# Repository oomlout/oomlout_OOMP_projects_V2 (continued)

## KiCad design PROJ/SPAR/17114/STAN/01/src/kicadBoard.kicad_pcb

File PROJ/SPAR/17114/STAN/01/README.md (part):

Contents
========

* [PRPR17114 > Qwiic Cellular Notecarrier](#prpr17114--qwiic-cellular-notecarrier)
	* [OOMP Parts](#oomp-parts)
	* [Images](#images)
	* [Tags](#tags)
  
![][im]
# PRPR17114 > Qwiic Cellular Notecarrier

- ID: PROJ-SPAR-17114-STAN-01
- Hex ID: PRPR17114
- Name: Qwiic Cellular Notecarrier
- Path: oomlout_OOMP_projects_V2/PROJ/SPAR/17114/STAN/01/
- Description: Qwiic Cellular Notecarrier
- Long Link: [http://oom.lt/PROJ-SPAR-17114-STAN-01](http://oom.lt/PROJ-SPAR-17114-STAN-01)
- Short Link: [http://oom.lt/PRPR17114](http://oom.lt/PRPR17114)

## OOMP Parts

|Image|OOMP ID|Designators|
| :--- | :--- | :--- |
||[CAPC-0603-X-NF100-V50](https://github.com/oomlout/oomlout_OOMP_parts_V2/tree/main/CAPC/0603/X/NF100/V50/)|[C6](https://github.com/oomlout/oomlout_OOMP_parts_V2/tree/main/CAPC/0603/X/NF100/V50/)|
||CAPC-0603-X-NF220-V25|C7|
||[CAPC-0603-X-UF1-V50](https://github.com/oomlout/oomlout_OOMP_parts_V2/tree/main/CAPC/0603/X/UF1/V50/)|[C5,C17,C18](https://github.com/oomlout/oomlout_OOMP_parts_V2/tree/main/CAPC/0603/X/UF1/V50/)|
||[CAPC-0603-X-UF47D-V16](https://github.com/oomlout/oomlout_OOMP_parts_V2/tree/main/CAPC/0603/X/UF47D/V16/)|[C4,C3](https://github.com/oomlout/oomlout_OOMP_parts_V2/tree/main/CAPC/0603/X/UF47D/V16/)|
||CAPX-1210-X-UF22-01|C1|
||DIOD-S323-X-UNMATCHED-01|D4,D1,D6|
||[HEAD-I01-X-PI01-01](https://github.com/oomlout/oomlout_OOMP_parts_V2/tree/main/HEAD/I01/X/PI01/01/)|[J13,J9](https://github.com/oomlout/oomlout_OOMP_parts_V2/tree/main/HEAD/I01/X/PI01/01/)|
||[HEAD-I01-X-PI02-01](https://github.com/oomlout/oomlout_OOMP_parts_V2/tree/main/HEAD/I01/X/PI02/01/)|[J4,J2,J7](https://github.com/oomlout/oomlout_OOMP_parts_V2/tree/main/HEAD/I01/X/PI02/01/)|
||[HEAD-I01-X-PI04-01](https://github.com/oomlout/oomlout_OOMP_parts_V2/tree/main/HEAD/I01/X/PI04/01/)|[J14](https://github.com/oomlout/oomlout_OOMP_parts_V2/tree/main/HEAD/I01/X/PI04/01/)|
||[HEAD-I01-X-PI06-01](https://github.com/oomlout/oomlout_OOMP_parts_V2/tree/main/HEAD/I01/X/PI06/01/)|[J6](https://github.com/oomlout/oomlout_OOMP_parts_V2/tree/main/HEAD/I01/X/PI06/01/)|
||[HEAD-I01-X-PI07-01](https://github.com/oomlout/oomlout_OOMP_parts_V2/tree/main/HEAD/I01/X/PI07/01/)|[J16](https://github.com/oomlout/oomlout_OOMP_parts_V2/tree/main/HEAD/I01/X/PI07/01/)|
||[HEAD-I01-X-PI10-01](https://github.com/oomlout/oomlout_OOMP_parts_V2/tree/main/HEAD/I01/X/PI10/01/)|[J5](https://github.com/oomlout/oomlout_OOMP_parts_V2/tree/main/HEAD/I01/X/PI10/01/)|
||HEAD-I01-X-UNMATCHED-01|J10,J12,J15|
||[HEAD-JSTSH-X-PI04-RS](https://github.com/oomlout/oomlout_OOMP_parts_V2/tree/main/HEAD/JSTSH/X/PI04/RS/)|[J8,J3](https://github.com/oomlout/oomlout_OOMP_parts_V2/tree/main/HEAD/JSTSH/X/PI04/RS/)|
||[LEDS-0603-R-STAN-01](https://github.com/oomlout/oomlout_OOMP_parts_V2/tree/main/LEDS/0603/R/STAN/01/)|[D5](https://github.com/oomlout/oomlout_OOMP_parts_V2/tree/main/LEDS/0603/R/STAN/01/)|
||[LEDS-0603-Y-STAN-01](https://github.com/oomlout/oomlout_OOMP_parts_V2/tree/main/LEDS/0603/Y/STAN/01/)|[D2](https://github.com/oomlout/oomlout_OOMP_parts_V2/tree/main/LEDS/0603/Y/STAN/01/)|
||[RESE-0603-X-O102-01](https://github.com/oomlout/oomlout_OOMP_parts_V2/tree/main/RESE/0603/X/O102/01/)|[R7,R11](https://github.com/oomlout/oomlout_OOMP_parts_V2/tree/main/RESE/0603/X/O102/01/)|
||[RESE-0603-X-O222-01](https://github.com/oomlout/oomlout_OOMP_parts_V2/tree/main/RESE/0603/X/O222/01/)|[R6,R4,R1](https://github.com/oomlout/oomlout_OOMP_parts_V2/tree/main/RESE/0603/X/O222/01/)|
||RESE-0603-X-O472-01|R3,R2|
||UNMATCHED-SO235-X-UNMATCHED-01|U1,U2|
||UNMATCHED-UNMATCHED-X-UNMATCHED-01|S1,E3,E4,U4|
||USBS-UNMATCHED-X-UNMATCHED-01|J1|
||||

## Images

|kicadPcb3dFront<br>|kicadPcb3dBack<br>|kicadPcb3d<br>|pcbdraw<br>|
| :---: | :---: | :---: | :---: |
|pcbdrawBack<br>||||

## Tags

|Tag Name|Tag Code|Tag Value|
| :--- | :--- | :--- |
|OOMP Type|oompType|PROJ|
|OOMP Size|oompSize|SPAR|
|OOMP Color|oompColor|17114|
|OOMP Description|oompDesc|STAN|
|OOMP Index|oompIndex|01|
|Full OOMP ID|oompID|PROJ-SPAR-17114-STAN-01|
|Hex ID (short code)|hexID|PRPR17114|
|name|name|Qwiic Cellular Notecarrier|
|gitRepo|gitRepo|https://github.com/sparkfun/Qwiic_Cellular-Notecarrier|
|gitName|gitName|Qwiic_Cellular-Notecarrier|
|eagleBoard|eagleBoard|/Hardware/Qwiic-Cellular-Notepad.brd|
|eagleSchem|eagleSchem|/Hardware/Qwiic-Cellular-Notepad.sch|
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
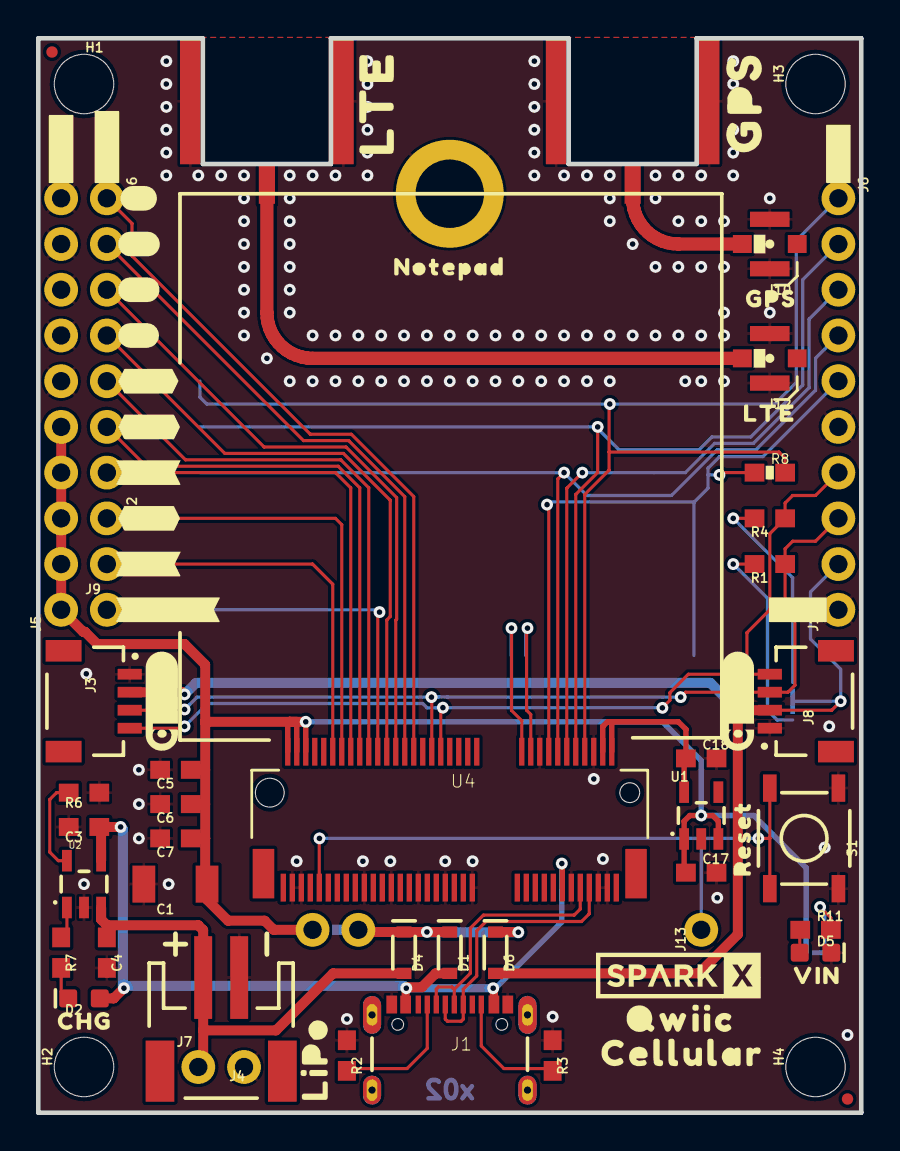
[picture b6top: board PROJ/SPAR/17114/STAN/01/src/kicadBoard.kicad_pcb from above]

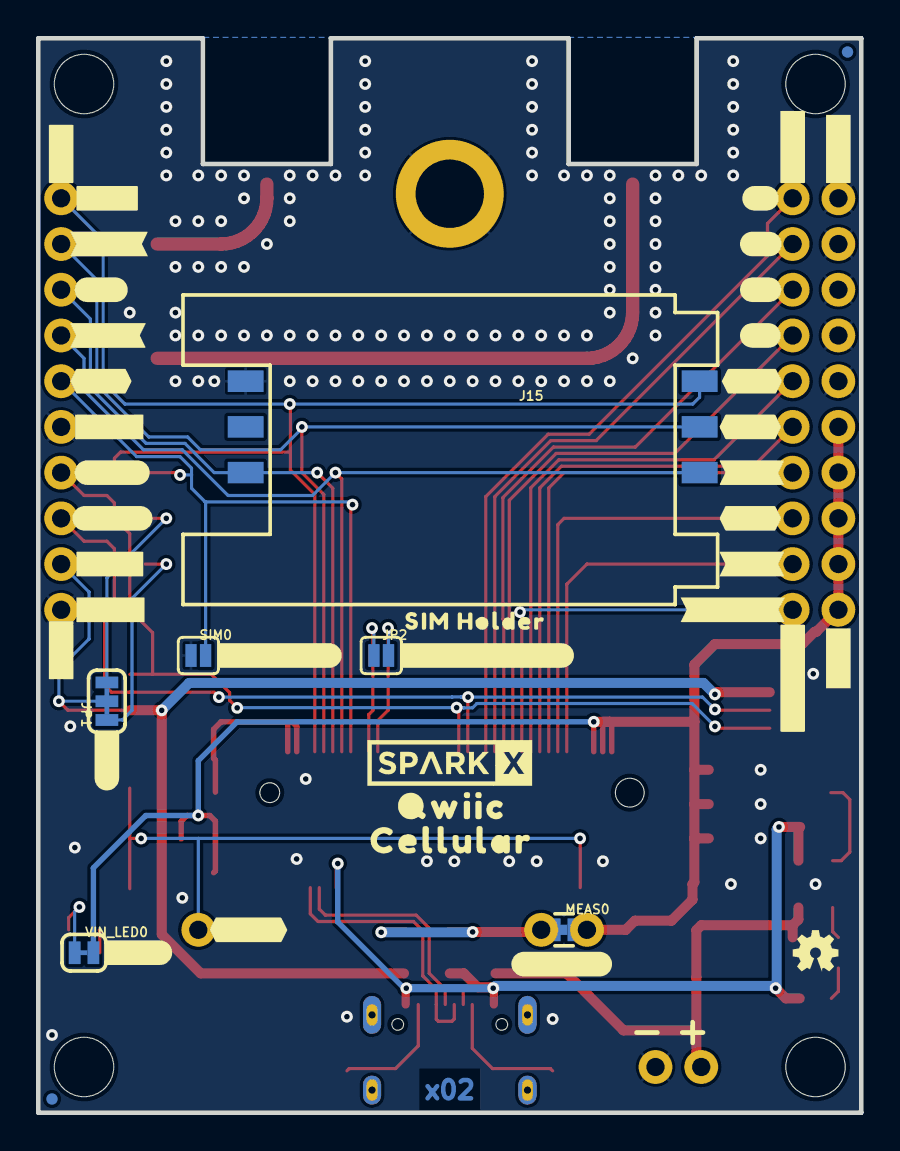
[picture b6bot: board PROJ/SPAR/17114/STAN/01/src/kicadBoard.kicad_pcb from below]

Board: 2 copper layers, 45.7 x 59.7 mm, 122 parts (45 on the bottom side), 40 nets.

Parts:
C1: 22uF; 1210
C3, C4: 4.7uF; 0603
C5, C17, C18: 1.0uF; 0603
C6: 0.1uF; 0603
C7: 0.22uF; 0603
D1, D4, D6: 3A/10V/280mV; SOD-323
D2: Yellow; LED-0603
D5: RED; LED-0603
E3, E4: SMA; SMA-EDGE-SMD
FD1, FD2, FD3, FD4: FIDUCIALUFIDUCIAL; FIDUCIAL-MICRO
FRAME1: FRAME-LEDGER; CREATIVE_COMMONS
H1, H2, H3, H4: STAND-OFF
H5: STAND-OFF; STAND-OFF-REFLOW-M2.5
J1: USB-C-16P-2LAYER-PADS
J2, J7: 1X02_NO_SILK
J3, J8: QWIIC_RIGHT_ANGLE; JST04_1MM_RA
J4: JST-2-SMD
J5: 1X10_NO_SILK
J6: External SIM; 1X06_NO_SILK
J9, J13: 1X01_NO_SILK
J10, J12: U.FL
J14: I2C; 1X04_NO_SILK
J15: SIM Socket; SIMHOLDER
J16: 1X07_NO_SILK
JP1: SMT-JUMPER_3_2-NC_TRACE_SILK
JP2: GPS_ANT_PWR; SMT-JUMPER_2_NO_SILK
LOGO2, LOGO5: QWIIC_LOGO_CONNECTOR; QWIIC_5.5MM
LOGO3: OSHW-LOGOMINI; OSHW-LOGO-MINI
MEAS0: COMBO-JUMPER_2_NC_TRACE
R1, R4, R6: 2.2k; 0603
R2, R3: 5.1k; 0603
R7, R11: 1k; 0603
R8: DNP; 0603-RES
S1: Reset; TACTILE_SWITCH_SMD_5.2MM
SIM0: SMT-JUMPER_2_NO_SILK
U1: STLQ015-3.3V; SOT23-5
U2: MCP73831; SOT23-5
U4: BLUES NOTECARD; M.2-CONNECTOR-E
U$1, U$41: #1#1
U$2: #3V3#2
U$3, U$18, U$22: #GND#0
U$4, U$42: #2#2
U$5, U$43: #3#3
U$6, U$44: #4#4
U$7: GPS_0
U$8: #SERIAL#1
U$9, U$53: #I�C_#0
U$10: #I�C#0
U$11, U$40: #AUX#0
U$12: LTE_1
U$13: #GND#3
U$14, U$46: #RX#6
U$15: LIPO0
U$16, U$47: #TX#5
U$17: #SCL#1
U$19, U$45: #EN#0
U$20: NOTEPAD0
U$21: #SDA#0
U$23: #VIN#0
U$24: #VACT_GPS#0
U$25: #SIM_CD#0
U$26, U$31: QWIIC0
U$27: SIM_HOLDER0
U$28: #MEAS#3
U$29, U$32: CELLULAR1
U$30: #RST#0
U$33: #VIN#1
U$34: ##CD##1
U$35: #1V8#4
U$36: #CLK#3
U$37: #IO#2
U$38: #RST#5
U$39, U$51: #SIM#0
U$48, U$52: #RX#0
U$49, U$54: #TX#1
U$50, U$55: #ATTN#2
U$56, U$57: SPARKX-LOGO4; SPARKX-MEDIUM
U$58: GPS0
U$59: LTE1
U$92: RESET1
U$94: VIN1
U$96: CHG1
VIN_LED0: SMT-JUMPER_2_NC_TRACE_SILK

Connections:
3.3V: D6.A, J3.2, J8.2, J14.2, JP1.2
ATTN: J9.1, U4.54
AUX1: J16.1, U4.46
AUX2: J16.2, U4.48
AUX3: J16.3, U4.50
AUX4: J16.4, U4.52
AUX_EN: J16.5, U4.56
AUX_RX: J16.6, U4.58
AUX_TX: J16.7, U4.60
CHG_LED: R7.1, U2.1
GND: C1.2, C3.2, C4.2, C5.2, C6.2, C7.2, C17.2, C18.2, D5.C, E3.GND@0, E3.GND@1, E4.GND@0, E4.GND@1, H5.1, J1.GND, J1.GND2, J3.1, J4.1, J5.6, J5.7, J5.8, J5.9, J5.10, J6.6, J7.2, J8.1, J10.1, J10.2, J12.1, J12.2, J14.1, J15.C5, R2.1, R3.1, R6.1, S1.1, S1.2, SIM0.1, U1.2, U2.2, U4.3, U4.5, U4.6, U4.11, U4.18, U4.33, U4.39, U4.45, U4.51, U4.57, U4.71, U4.73
unnamed: JP1.3, R4.2
unnamed: JP1.1, R1.2
unnamed: D2.C, R7.2
unnamed: D5.A, R11.1
unnamed: R11.2, VIN_LED0.1
unnamed: R6.2, U2.5
unnamed: J1.A5, R2.2
unnamed: J1.B5, R3.2
RF_GPS: E4.SIG, J10.FEED
RF_LTE: E3.SIG, J12.FEED
RX: J2.1, U4.62
SCL: J3.4, J8.4, J14.4, R4.1, U4.40
SDA: J3.3, J8.3, J14.3, R1.1, U4.42
SIM_CLK: J6.4, J15.C3, U4.14
SIM_IO: J6.3, J15.C7, U4.12
SIM_RST: J6.2, J15.C2, U4.10
SIM_VCC: J6.1, J15.C1, R8.2, U4.8
SIM_~CD: J6.5, R8.1, SIM0.2, U4.16
TX: J2.2, U4.64
USB_D+: J1.A6, J1.B6, U4.7
USB_D-: J1.A7, J1.B7, U4.9
VACT_GPS_IN: JP2.2, U4.22
VACT_GPS_OUT: JP2.1, U4.20
VIN: C1.1, C5.1, C6.1, C7.1, C17.1, J5.1, J5.2, J5.3, J5.4, J5.5, MEAS0.2, MEAS0.4, U1.1, U1.3, U4.70, U4.72, U4.74, VIN_LED0.2
VIN1: D1.C, D4.C, D6.C, MEAS0.1, MEAS0.3
VIO: C18.1, U1.5, U4.2, U4.4
V_BATT: C4.1, D4.A, J4.2, J7.1, U2.3
V_USB: C3.1, D1.A, D2.A, J1.VBUS1, J1.VBUS2, U2.4, U4.13
~RESET: J13.1, S1.3, S1.4, U4.67

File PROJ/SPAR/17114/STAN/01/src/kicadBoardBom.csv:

"Id";"Designator";"Package";"Quantity";"Designation";"Supplier and ref";
1;"U$31,U$26";"QWIIC0";2;"";;;
2;"FD2,FD1,FD3,FD4";"FIDUCIAL-MICRO";4;"FIDUCIALUFIDUCIAL";;;
3;"U$53,U$9";"#I�C_#0";2;"";;;
4;"H2,H4,H3,H1";"STAND-OFF";4;"STAND-OFF";;;
5;"U$96";"CHG1";1;"";;;
6;"J5";"1X10_NO_SILK";1;"";;;
7;"R3,R2";"0603";2;"5.1k";;;
8;"U$20";"NOTEPAD0";1;"";;;
9;"U$92";"RESET1";1;"";;;
10;"U$50,U$55";"#ATTN#2";2;"";;;
11;"R7,R11";"0603";2;"1k";;;
12;"J14";"1X04_NO_SILK";1;"I2C";;;
13;"U$22,U$18,U$3";"#GND#0";3;"";;;
14;"U$51,U$39";"#SIM#0";2;"";;;
15;"J1";"USB-C-16P-2LAYER-PADS";1;"";;;
16;"U$7";"GPS_0";1;"";;;
17;"U1";"SOT23-5";1;"STLQ015-3.3V";;;
18;"S1";"TACTILE_SWITCH_SMD_5.2MM";1;"Reset";;;
19;"R8";"0603-RES";1;"DNP";;;
20;"J13,J9";"1X01_NO_SILK";2;"";;;
21;"D4,D1,D6";"SOD-323";3;"3A/10V/280mV";;;
22;"J16";"1X07_NO_SILK";1;"";;;
23;"E3,E4";"SMA-EDGE-SMD";2;"SMA";;;
24;"U$59";"LTE1";1;"";;;
25;"R6,R4,R1";"0603";3;"2.2k";;;
26;"U$40,U$11";"#AUX#0";2;"";;;
27;"U$94";"VIN1";1;"";;;
28;"C1";"1210";1;"22uF";;;
29;"U$58";"GPS0";1;"";;;
30;"J4";"JST-2-SMD";1;"";;;
31;"U$41,U$1";"#1#1";2;"";;;
32;"LOGO5,LOGO2";"QWIIC_5.5MM";2;"QWIIC_LOGO_CONNECTOR";;;
33;"J6";"1X06_NO_SILK";1;"External SIM";;;
34;"U$56,U$57";"SPARKX-MEDIUM";2;"SPARKX-LOGO4";;;
35;"J2,J7";"1X02_NO_SILK";2;"";;;
36;"U$44,U$6";"#4#4";2;"";;;
37;"U$48,U$52";"#RX#0";2;"";;;
38;"U$49,U$54";"#TX#1";2;"";;;
39;"J8,J3";"JST04_1MM_RA";2;"QWIIC_RIGHT_ANGLE";;;
40;"C6";"0603";1;"0.1uF";;;
41;"U$46,U$14";"#RX#6";2;"";;;
42;"U$12";"LTE_1";1;"";;;
43;"U$42,U$4";"#2#2";2;"";;;
44;"J10,J12";"U.FL";2;"U.FL";;;
45;"U$43,U$5";"#3#3";2;"";;;
46;"H5";"STAND-OFF-REFLOW-M2.5";1;"STAND-OFF";;;
47;"U2";"SOT23-5";1;"MCP73831";;;
48;"U4";"M.2-CONNECTOR-E";1;"BLUES NOTECARD";;;
49;"C4,C3";"0603";2;"4.7uF";;;
50;"U$47,U$16";"#TX#5";2;"";;;
51;"C5,C17,C18";"0603";3;"1.0uF";;;
52;"U$45,U$19";"#EN#0";2;"";;;
53;"D5";"LED-0603";1;"RED";;;
54;"FRAME1";"CREATIVE_COMMONS";1;"FRAME-LEDGER";;;
55;"U$29,U$32";"CELLULAR1";2;"";;;
56;"D2";"LED-0603";1;"Yellow";;;
57;"C7";"0603";1;"0.22uF";;;
58;"U$15";"LIPO0";1;"";;;
59;"MEAS0";"COMBO-JUMPER_2_NC_TRACE";1;"";;;
60;"JP1";"SMT-JUMPER_3_2-NC_TRACE_SILK";1;"";;;
61;"U$25";"#SIM_CD#0";1;"";;;
62;"LOGO3";"OSHW-LOGO-MINI";1;"OSHW-LOGOMINI";;;
63;"SIM0";"SMT-JUMPER_2_NO_SILK";1;"";;;
64;"U$36";"#CLK#3";1;"";;;
65;"U$37";"#IO#2";1;"";;;
66;"JP2";"SMT-JUMPER_2_NO_SILK";1;"GPS_ANT_PWR";;;
67;"U$2";"#3V3#2";1;"";;;
68;"U$30";"#RST#0";1;"";;;
69;"U$23";"#VIN#0";1;"";;;
70;"J15";"SIMHOLDER";1;"SIM Socket";;;
71;"U$28";"#MEAS#3";1;"";;;
72;"U$17";"#SCL#1";1;"";;;
73;"U$8";"#SERIAL#1";1;"";;;
74;"U$21";"#SDA#0";1;"";;;
75;"U$35";"#1V8#4";1;"";;;
76;"U$33";"#VIN#1";1;"";;;
77;"U$38";"#RST#5";1;"";;;
78;"U$27";"SIM_HOLDER0";1;"";;;
79;"VIN_LED0";"SMT-JUMPER_2_NC_TRACE_SILK";1;"";;;
80;"U$10";"#I�C#0";1;"";;;
81;"U$13";"#GND#3";1;"";;;
82;"U$24";"#VACT_GPS#0";1;"";;;
83;"U$34";"##CD##1";1;"";;;

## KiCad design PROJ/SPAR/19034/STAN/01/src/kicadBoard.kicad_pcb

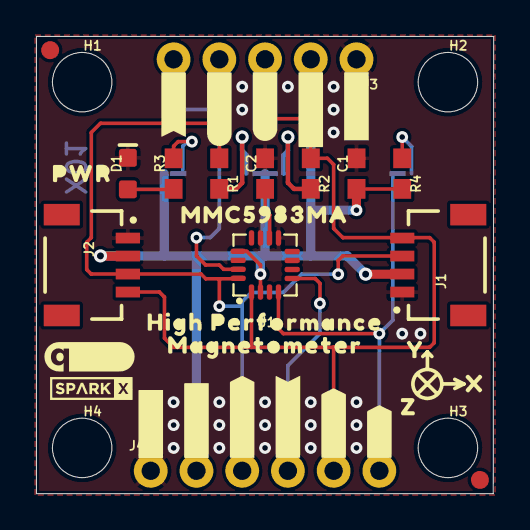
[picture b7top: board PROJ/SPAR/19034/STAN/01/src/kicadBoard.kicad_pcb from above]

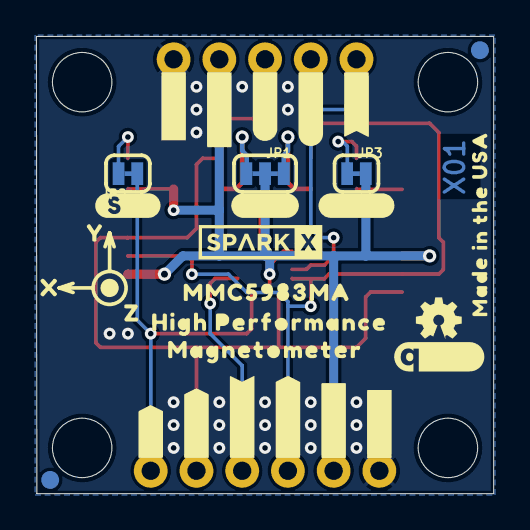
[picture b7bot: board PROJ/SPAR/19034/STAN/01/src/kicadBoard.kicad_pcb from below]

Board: 2 copper layers, 25.4 x 25.4 mm, 68 parts (29 on the bottom side), 13 nets.

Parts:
C1: 0.1uF; 0603
C2: 10uF; 0603
D1: RED; LED-0603
FD1, FD2, FD3, FD4: FIDUCIAL1X2; FIDUCIAL-1X2
FRAME1: FRAME-LETTERNO_PACKAGE; DUMMY
H1, H2, H3, H4: STAND-OFF
J1, J2: Qwiic; JST04_1MM_RA
J3: 1X05_NO_SILK
J4: 1X06_NO_SILK
JP1: JUMPER-SMT_3_2-NC_TRACE_SILK; SMT-JUMPER_3_2-NC_TRACE_SILK
JP2, JP3: JUMPER-SMT_2_NC_TRACE_SILK; SMT-JUMPER_2_NC_TRACE_SILK
LOGO1: OSHW-LOGOMINI; OSHW-LOGO-MINI
LOGO2, LOGO3: QWIIC_LOGO_5MM; QWIIC_5MM
R1, R2: 2.2k; 0603
R3: 1k; 0603
R4: 10k; 0603
U1: MMC5983MA_QFN16; LGA-16-3X3MM-4X4PINS
U$1, U$10: HIGH_PERFORMANCE11
U$2, U$35: #SCL#6
U$3, U$12, U$18, U$29: #3#3V#0
U$4, U$13, U$17, U$28: #GND#4
U$5, U$38: #SDA#5
U$6, U$31: #CIPO#11
U$7, U$16: #INT#7
U$8: PWR9
U$9, U$30: #COPI#12
U$11, U$24: MAGNETOMETER12
U$14, U$32: #SCK#13
U$15, U$33: ##CS##10
U$19, U$26: Y16
U$20, U$25: X15
U$21: #LED#8
U$22: #I2C#9
U$23: #SPI#9
U$27, U$39: Z17
U$34: MADE_IN_THE_USA20
U$36: SPARKX-LOGO2; SPARKX-TINY
U$37: SPARKX-LOGO3; SPARKX-SMALL
U$41, U$42: MMC5983MA0

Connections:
3.3V: C1.1, J1.2, J2.2, J3.2, J4.2, JP1.2, JP3.2, R4.2, U1.2, U1.13
CAP: C2.1, U1.10
CIPO: J4.4, U1.5
GND: C1.2, C2.2, D1.C, J1.1, J2.1, J3.1, J4.1, U1.9, U1.11
INT: J3.5, U1.15
unnamed: JP3.1, R3.2
unnamed: JP1.1, R2.2
unnamed: JP1.3, R1.2
unnamed: D1.A, R3.1
unnamed: JP2.2, R4.1
SCL/SCK: J1.4, J2.4, J3.3, J4.5, R2.1, U1.1
SDA/COPI: J1.3, J2.3, J3.4, J4.3, R1.1, U1.16
~CS: J4.6, JP2.1, U1.4

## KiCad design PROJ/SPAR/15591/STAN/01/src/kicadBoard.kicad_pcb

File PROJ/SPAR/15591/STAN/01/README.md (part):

Contents
========

* [PRPR15591 > Qwiic Switch](#prpr15591--qwiic-switch)
	* [OOMP Parts](#oomp-parts)
	* [Images](#images)
	* [Tags](#tags)
  
![][im]
# PRPR15591 > Qwiic Switch

- ID: PROJ-SPAR-15591-STAN-01
- Hex ID: PRPR15591
- Name: Qwiic Switch
- Path: oomlout_OOMP_projects_V2/PROJ/SPAR/15591/STAN/01/
- Description: Qwiic Switch
- Long Link: [http://oom.lt/PROJ-SPAR-15591-STAN-01](http://oom.lt/PROJ-SPAR-15591-STAN-01)
- Short Link: [http://oom.lt/PRPR15591](http://oom.lt/PRPR15591)

## OOMP Parts

|Image|OOMP ID|Designators|
| :--- | :--- | :--- |
||[CAPC-0603-X-NF100-V50](https://github.com/oomlout/oomlout_OOMP_parts_V2/tree/main/CAPC/0603/X/NF100/V50/)|[C2](https://github.com/oomlout/oomlout_OOMP_parts_V2/tree/main/CAPC/0603/X/NF100/V50/)|
||[HEAD-I01-X-PI01-01](https://github.com/oomlout/oomlout_OOMP_parts_V2/tree/main/HEAD/I01/X/PI01/01/)|[J5](https://github.com/oomlout/oomlout_OOMP_parts_V2/tree/main/HEAD/I01/X/PI01/01/)|
||[HEAD-I01-X-PI02-01](https://github.com/oomlout/oomlout_OOMP_parts_V2/tree/main/HEAD/I01/X/PI02/01/)|[J4](https://github.com/oomlout/oomlout_OOMP_parts_V2/tree/main/HEAD/I01/X/PI02/01/)|
||[HEAD-I01-X-PI04-01](https://github.com/oomlout/oomlout_OOMP_parts_V2/tree/main/HEAD/I01/X/PI04/01/)|[J1](https://github.com/oomlout/oomlout_OOMP_parts_V2/tree/main/HEAD/I01/X/PI04/01/)|
||HEAD-I01-X-UNMATCHED-01|J7|
||[HEAD-JSTSH-X-PI04-RS](https://github.com/oomlout/oomlout_OOMP_parts_V2/tree/main/HEAD/JSTSH/X/PI04/RS/)|[J3,J2](https://github.com/oomlout/oomlout_OOMP_parts_V2/tree/main/HEAD/JSTSH/X/PI04/RS/)|
||[LEDS-0603-R-STAN-01](https://github.com/oomlout/oomlout_OOMP_parts_V2/tree/main/LEDS/0603/R/STAN/01/)|[D1](https://github.com/oomlout/oomlout_OOMP_parts_V2/tree/main/LEDS/0603/R/STAN/01/)|
||[MCUU-SC14-84-ATTINY-01](https://github.com/oomlout/oomlout_OOMP_parts_V2/tree/main/MCUU/SC14/84/ATTINY/01/)|[U4](https://github.com/oomlout/oomlout_OOMP_parts_V2/tree/main/MCUU/SC14/84/ATTINY/01/)|
||[RESE-0603-X-O102-01](https://github.com/oomlout/oomlout_OOMP_parts_V2/tree/main/RESE/0603/X/O102/01/)|[R4](https://github.com/oomlout/oomlout_OOMP_parts_V2/tree/main/RESE/0603/X/O102/01/)|
||[RESE-0603-X-O103-01](https://github.com/oomlout/oomlout_OOMP_parts_V2/tree/main/RESE/0603/X/O103/01/)|[R11,R3](https://github.com/oomlout/oomlout_OOMP_parts_V2/tree/main/RESE/0603/X/O103/01/)|
||[RESE-0603-X-O222-01](https://github.com/oomlout/oomlout_OOMP_parts_V2/tree/main/RESE/0603/X/O222/01/)|[R2,R1](https://github.com/oomlout/oomlout_OOMP_parts_V2/tree/main/RESE/0603/X/O222/01/)|
||||

## Images

|kicadPcb3dFront<br>|kicadPcb3dBack<br>|kicadPcb3d<br>|pcbdraw<br>|
| :---: | :---: | :---: | :---: |
|pcbdrawBack<br>||||

## Tags

|Tag Name|Tag Code|Tag Value|
| :--- | :--- | :--- |
|OOMP Type|oompType|PROJ|
|OOMP Size|oompSize|SPAR|
|OOMP Color|oompColor|15591|
|OOMP Description|oompDesc|STAN|
|OOMP Index|oompIndex|01|
|Full OOMP ID|oompID|PROJ-SPAR-15591-STAN-01|
|Hex ID (short code)|hexID|PRPR15591|
|name|name|Qwiic Switch|
|gitRepo|gitRepo|https://github.com/sparkfun/Qwiic_Switch|
|gitName|gitName|Qwiic_Switch|
|eagleBoard|eagleBoard|/Hardware/Qwiic_Switch.brd|
|eagleSchem|eagleSchem|/Hardware/Qwiic_Switch.sch|
|OOMP Parts List|oompParts|<table><tr><td>'J7'</td></tr><tr><td> <table><tr><td>'OOMPID'</td></tr><tr><td> 'HEAD-I01-X-UNMATCHED-01'</td><td> 'FULL'</td></tr><tr><td> <table><tr><td>'DESC'</td></tr><tr><td> ''</td><td> 'PART'</td></tr><tr><td> 'J7'</td><td> 'DEVICE'</td></tr><tr><td> '2X3_TEST_POINTS ISP'</td><td> 'PACKAGE'</td></tr><tr><td> '2X3_TEST_POINTS'</td><td> 'PARTLETTER'</td></tr><tr><td> 'J'</td><td> 'VALUE'</td></tr><tr><td> 'ISP'</td><td> 'VALUENUMBER'</td></tr><tr><td> ''</td><td> 'PACKAGENUMBER'</td></tr><tr><td> '23'</td><td> 'BOM'</td></tr><tr><td> ''</td><td> 'OWNER'</td></tr><tr><td> 'SPAR'</td><td> 'FULL'</td></tr><tr><td> 'J7</td><td>ISP</td><td>2X3_TEST_POINTS ISP</td><td>2X3_TEST_POINTS</td><td></td><td></td><td>'</td></tr></table></td></tr></table></td><td> 'D1'</td></tr><tr><td> <table><tr><td>'OOMPID'</td></tr><tr><td> 'LEDS-0603-R-STAN-01'</td><td> 'FULL'</td></tr><tr><td> <table><tr><td>'DESC'</td></tr><tr><td> ''</td><td> 'PART'</td></tr><tr><td> 'D1'</td><td> 'DEVICE'</td></tr><tr><td> 'LED-0603 RED'</td><td> 'PACKAGE'</td></tr><tr><td> 'LED-0603'</td><td> 'PARTLETTER'</td></tr><tr><td> 'D'</td><td> 'VALUE'</td></tr><tr><td> 'RED'</td><td> 'VALUENUMBER'</td></tr><tr><td> ''</td><td> 'PACKAGENUMBER'</td></tr><tr><td> '0603'</td><td> 'BOM'</td></tr><tr><td> ''</td><td> 'OWNER'</td></tr><tr><td> 'SPAR'</td><td> 'FULL'</td></tr><tr><td> 'D1</td><td>RED</td><td>LED-0603 RED</td><td>LED-0603</td><td></td><td></td><td>'</td></tr></table></td></tr></table></td><td> 'U4'</td></tr><tr><td> <table><tr><td>'OOMPID'</td></tr><tr><td> 'MCUU-SC14-84-ATTINY-01'</td><td> 'FULL'</td></tr><tr><td> <table><tr><td>'DESC'</td></tr><tr><td> ''</td><td> 'PART'</td></tr><tr><td> 'U4'</td><td> 'DEVICE'</td></tr><tr><td> 'SO14 ATTINY84-ARDUINO'</td><td> 'PACKAGE'</td></tr><tr><td> 'SO14'</td><td> 'PARTLETTER'</td></tr><tr><td> 'U'</td><td> 'VALUE'</td></tr><tr><td> 'ATTINY84-ARDUINO'</td><td> 'VALUENUMBER'</td></tr><tr><td> '84-'</td><td> 'PACKAGENUMBER'</td></tr><tr><td> '14'</td><td> 'BOM'</td></tr><tr><td> ''</td><td> 'OWNER'</td></tr><tr><td> 'SPAR'</td><td> 'FULL'</td></tr><tr><td> 'U4</td><td>ATTINY84-ARDUINO</td><td>SO14 ATTINY84-ARDUINO</td><td>SO14</td><td></td><td></td><td>'</td></tr></table></td></tr></table></td><td> 'J5'</td></tr><tr><td> <table><tr><td>'OOMPID'</td></tr><tr><td> 'HEAD-I01-X-PI01-01'</td><td> 'FULL'</td></tr><tr><td> <table><tr><td>'DESC'</td></tr><tr><td> ''</td><td> 'PART'</td></tr><tr><td> 'J5'</td><td> 'DEVICE'</td></tr><tr><td> '1X01_NO_SILK '</td><td> 'PACKAGE'</td></tr><tr><td> '1X01_NO_SILK'</td><td> 'PARTLETTER'</td></tr><tr><td> 'J'</td><td> 'VALUE'</td></tr><tr><td> ''</td><td> 'VALUENUMBER'</td></tr><tr><td> ''</td><td> 'PACKAGENUMBER'</td></tr><tr><td> '101'</td><td> 'BOM'</td></tr><tr><td> ''</td><td> 'OWNER'</td></tr><tr><td> 'SPAR'</td><td> 'FULL'</td></tr><tr><td> 'J5</td><td></td><td>1X01_NO_SILK </td><td>1X01_NO_SILK</td><td></td><td></td><td>'</td></tr></table></td></tr></table></td><td> 'R2'</td></tr><tr><td> <table><tr><td>'OOMPID'</td></tr><tr><td> 'RESE-0603-X-O222-01'</td><td> 'FULL'</td></tr><tr><td> <table><tr><td>'DESC'</td></tr><tr><td> ''</td><td> 'PART'</td></tr><tr><td> 'R2'</td><td> 'DEVICE'</td></tr><tr><td> '0603 2.2k'</td><td> 'PACKAGE'</td></tr><tr><td> '0603'</td><td> 'PARTLETTER'</td></tr><tr><td> 'R'</td><td> 'VALUE'</td></tr><tr><td> '2.2k'</td><td> 'VALUENUMBER'</td></tr><tr><td> '2.2'</td><td> 'PACKAGENUMBER'</td></tr><tr><td> '0603'</td><td> 'BOM'</td></tr><tr><td> ''</td><td> 'OWNER'</td></tr><tr><td> 'SPAR'</td><td> 'FULL'</td></tr><tr><td> 'R2</td><td>2.2k</td><td>0603 2.2k</td><td>0603</td><td></td><td></td><td>'</td></tr></table></td></tr></table></td><td> 'R1'</td></tr><tr><td> <table><tr><td>'OOMPID'</td></tr><tr><td> 'RESE-0603-X-O222-01'</td><td> 'FULL'</td></tr><tr><td> <table><tr><td>'DESC'</td></tr><tr><td> ''</td><td> 'PART'</td></tr><tr><td> 'R1'</td><td> 'DEVICE'</td></tr><tr><td> '0603 2.2k'</td><td> 'PACKAGE'</td></tr><tr><td> '0603'</td><td> 'PARTLETTER'</td></tr><tr><td> 'R'</td><td> 'VALUE'</td></tr><tr><td> '2.2k'</td><td> 'VALUENUMBER'</td></tr><tr><td> '2.2'</td><td> 'PACKAGENUMBER'</td></tr><tr><td> '0603'</td><td> 'BOM'</td></tr><tr><td> ''</td><td> 'OWNER'</td></tr><tr><td> 'SPAR'</td><td> 'FULL'</td></tr><tr><td> 'R1</td><td>2.2k</td><td>0603 2.2k</td><td>0603</td><td></td><td></td><td>'</td></tr></table></td></tr></table></td><td> 'C2'</td></tr><tr><td> <table><tr><td>'OOMPID'</td></tr><tr><td> 'CAPC-0603-X-NF100-V50'</td><td> 'FULL'</td></tr><tr><td> <table><tr><td>'DESC'</td></tr><tr><td> ''</td><td> 'PART'</td></tr><tr><td> 'C2'</td><td> 'DEVICE'</td></tr><tr><td> '0603 0.1uF'</td><td> 'PACKAGE'</td></tr><tr><td> '0603'</td><td> 'PARTLETTER'</td></tr><tr><td> 'C'</td><td> 'VALUE'</td></tr><tr><td> '0.1uF'</td><td> 'VALUENUMBER'</td></tr><tr><td> '0.1'</td><td> 'PACKAGENUMBER'</td></tr><tr><td> '0603'</td><td> 'BOM'</td></tr><tr><td> ''</td><td> 'OWNER'</td></tr><tr><td> 'SPAR'</td><td> 'FULL'</td></tr><tr><td> 'C2</td><td>0.1uF</td><td>0603 0.1uF</td><td>0603</td><td></td><td></td><td>'</td></tr></table></td></tr></table></td><td> 'R4'</td></tr><tr><td> <table><tr><td>'OOMPID'</td></tr><tr><td> 'RESE-0603-X-O102-01'</td><td> 'FULL'</td></tr><tr><td> <table><tr><td>'DESC'</td></tr><tr><td> ''</td><td> 'PART'</td></tr><tr><td> 'R4'</td><td> 'DEVICE'</td></tr><tr><td> '0603 1k'</td><td> 'PACKAGE'</td></tr><tr><td> '0603'</td><td> 'PARTLETTER'</td></tr><tr><td> 'R'</td><td> 'VALUE'</td></tr><tr><td> '1k'</td><td> 'VALUENUMBER'</td></tr><tr><td> '1'</td><td> 'PACKAGENUMBER'</td></tr><tr><td> '0603'</td><td> 'BOM'</td></tr><tr><td> ''</td><td> 'OWNER'</td></tr><tr><td> 'SPAR'</td><td> 'FULL'</td></tr><tr><td> 'R4</td><td>1k</td><td>0603 1k</td><td>0603</td><td></td><td></td><td>'</td></tr></table></td></tr></table></td><td> 'J4'</td></tr><tr><td> <table><tr><td>'OOMPID'</td></tr><tr><td> 'HEAD-I01-X-PI02-01'</td><td> 'FULL'</td></tr><tr><td> <table><tr><td>'DESC'</td></tr><tr><td> ''</td><td> 'PART'</td></tr><tr><td> 'J4'</td><td> 'DEVICE'</td></tr><tr><td> '1X02_NO_SILK '</td><td> 'PACKAGE'</td></tr><tr><td> '1X02_NO_SILK'</td><td> 'PARTLETTER'</td></tr><tr><td> 'J'</td><td> 'VALUE'</td></tr><tr><td> ''</td><td> 'VALUENUMBER'</td></tr><tr><td> ''</td><td> 'PACKAGENUMBER'</td></tr><tr><td> '102'</td><td> 'BOM'</td></tr><tr><td> ''</td><td> 'OWNER'</td></tr><tr><td> 'SPAR'</td><td> 'FULL'</td></tr><tr><td> 'J4</td><td></td><td>1X02_NO_SILK </td><td>1X02_NO_SILK</td><td></td><td></td><td>'</td></tr></table></td></tr></table></td><td> 'R11'</td></tr><tr><td> <table><tr><td>'OOMPID'</td></tr><tr><td> 'RESE-0603-X-O103-01'</td><td> 'FULL'</td></tr><tr><td> <table><tr><td>'DESC'</td></tr><tr><td> ''</td><td> 'PART'</td></tr><tr><td> 'R11'</td><td> 'DEVICE'</td></tr><tr><td> '0603 10k'</td><td> 'PACKAGE'</td></tr><tr><td> '0603'</td><td> 'PARTLETTER'</td></tr><tr><td> 'R'</td><td> 'VALUE'</td></tr><tr><td> '10k'</td><td> 'VALUENUMBER'</td></tr><tr><td> '10'</td><td> 'PACKAGENUMBER'</td></tr><tr><td> '0603'</td><td> 'BOM'</td></tr><tr><td> ''</td><td> 'OWNER'</td></tr><tr><td> 'SPAR'</td><td> 'FULL'</td></tr><tr><td> 'R11</td><td>10k</td><td>0603 10k</td><td>0603</td><td></td><td></td><td>'</td></tr></table></td></tr></table></td><td> 'R3'</td></tr><tr><td> <table><tr><td>'OOMPID'</td></tr><tr><td> 'RESE-0603-X-O103-01'</td><td> 'FULL'</td></tr><tr><td> <table><tr><td>'DESC'</td></tr><tr><td> ''</td><td> 'PART'</td></tr><tr><td> 'R3'</td><td> 'DEVICE'</td></tr><tr><td> '0603 10k'</td><td> 'PACKAGE'</td></tr><tr><td> '0603'</td><td> 'PARTLETTER'</td></tr><tr><td> 'R'</td><td> 'VALUE'</td></tr><tr><td> '10k'</td><td> 'VALUENUMBER'</td></tr><tr><td> '10'</td><td> 'PACKAGENUMBER'</td></tr><tr><td> '0603'</td><td> 'BOM'</td></tr><tr><td> ''</td><td> 'OWNER'</td></tr><tr><td> 'SPAR'</td><td> 'FULL'</td></tr><tr><td> 'R3</td><td>10k</td><td>0603 10k</td><td>0603</td><td></td><td></td><td>'</td></tr></table></td></tr></table></td><td> 'J1'</td></tr><tr><td> <table><tr><td>'OOMPID'</td></tr><tr><td> 'HEAD-I01-X-PI04-01'</td><td> 'FULL'</td></tr><tr><td> <table><tr><td>'DESC'</td></tr><tr><td> ''</td><td> 'PART'</td></tr><tr><td> 'J1'</td><td> 'DEVICE'</td></tr><tr><td> '1X04_NO_SILK '</td><td> 'PACKAGE'</td></tr><tr><td> '1X04_NO_SILK'</td><td> 'PARTLETTER'</td></tr><tr><td> 'J'</td><td> 'VALUE'</td></tr><tr><td> ''</td><td> 'VALUENUMBER'</td></tr><tr><td> ''</td><td> 'PACKAGENUMBER'</td></tr><tr><td> '104'</td><td> 'BOM'</td></tr><tr><td> ''</td><td> 'OWNER'</td></tr><tr><td> 'SPAR'</td><td> 'FULL'</td></tr><tr><td> 'J1</td><td></td><td>1X04_NO_SILK </td><td>1X04_NO_SILK</td><td></td><td></td><td>'</td></tr></table></td></tr></table></td><td> 'J3'</td></tr><tr><td> <table><tr><td>'OOMPID'</td></tr><tr><td> 'HEAD-JSTSH-X-PI04-RS'</td><td> 'FULL'</td></tr><tr><td> <table><tr><td>'DESC'</td></tr><tr><td> ''</td><td> 'PART'</td></tr><tr><td> 'J3'</td><td> 'DEVICE'</td></tr><tr><td> 'JST04_1MM_RA '</td><td> 'PACKAGE'</td></tr><tr><td> 'JST04_1MM_RA'</td><td> 'PARTLETTER'</td></tr><tr><td> 'J'</td><td> 'VALUE'</td></tr><tr><td> ''</td><td> 'VALUENUMBER'</td></tr><tr><td> ''</td><td> 'PACKAGENUMBER'</td></tr><tr><td> '041'</td><td> 'BOM'</td></tr><tr><td> ''</td><td> 'OWNER'</td></tr><tr><td> 'SPAR'</td><td> 'FULL'</td></tr><tr><td> 'J3</td><td></td><td>JST04_1MM_RA </td><td>JST04_1MM_RA</td><td></td><td></td><td>'</td></tr></table></td></tr></table></td><td> 'J2'</td></tr><tr><td> <table><tr><td>'OOMPID'</td></tr><tr><td> 'HEAD-JSTSH-X-PI04-RS'</td><td> 'FULL'</td></tr><tr><td> <table><tr><td>'DESC'</td></tr><tr><td> ''</td><td> 'PART'</td></tr><tr><td> 'J2'</td><td> 'DEVICE'</td></tr><tr><td> 'JST04_1MM_RA '</td><td> 'PACKAGE'</td></tr><tr><td> 'JST04_1MM_RA'</td><td> 'PARTLETTER'</td></tr><tr><td> 'J'</td><td> 'VALUE'</td></tr><tr><td> ''</td><td> 'VALUENUMBER'</td></tr><tr><td> ''</td><td> 'PACKAGENUMBER'</td></tr><tr><td> '041'</td><td> 'BOM'</td></tr><tr><td> ''</td><td> 'OWNER'</td></tr><tr><td> 'SPAR'</td><td> 'FULL'</td></tr><tr><td> 'J2</td><td></td><td>JST04_1MM_RA </td><td>JST04_1MM_RA</td><td></td><td></td><td>'</td></tr></table></td></tr></table></td></tr></table>|
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
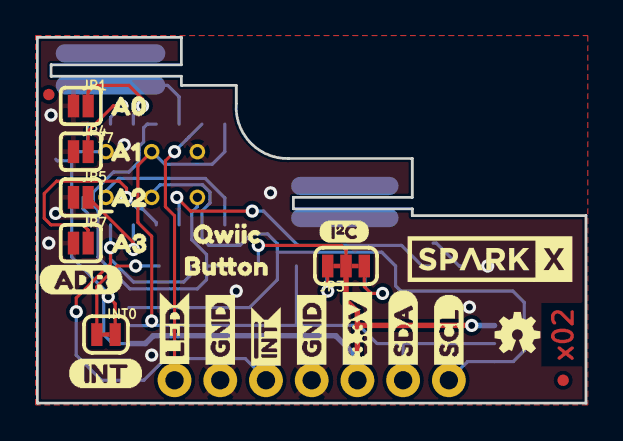
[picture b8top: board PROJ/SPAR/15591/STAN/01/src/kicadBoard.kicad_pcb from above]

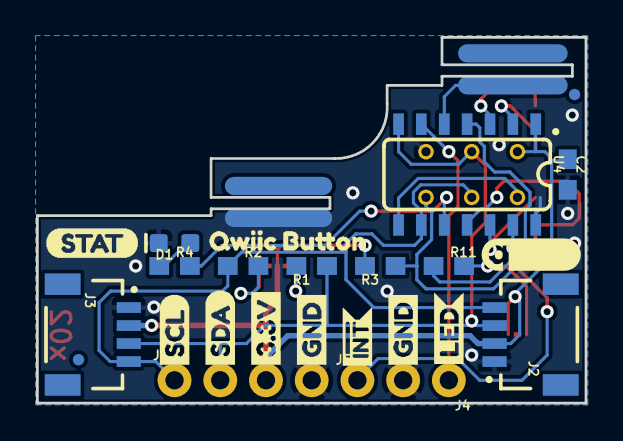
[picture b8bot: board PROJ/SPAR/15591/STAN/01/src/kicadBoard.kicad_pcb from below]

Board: 2 copper layers, 30.5 x 20.3 mm, 54 parts (27 on the bottom side), 17 nets.

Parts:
C2: 0.1uF; 0603
D1: RED; LED-0603
FRAME1: FRAME-LETTER; CREATIVE_COMMONS
INT0: SMT-JUMPER_2_NC_TRACE_SILK
J1: 1X04_NO_SILK
J2, J3: JST04_1MM_RA
J4: 1X02_NO_SILK
J5: 1X01_NO_SILK
J7: ISP; 2X3_TEST_POINTS
JP1, JP4, JP5, JP7: SMT-JUMPER_2_NO_SILK
JP2, JP6, JP8, JP9: FIDUCIALUFIDUCIAL; MICRO-FIDUCIAL
JP3: SMT-JUMPER_3_2-NC_TRACE_SILK
LOGO1: OSHW-LOGOMINI; OSHW-LOGO-MINI
R1, R2: 2.2k; 0603
R3, R11: 10k; 0603
R4: 1k; 0603
U4: ATTINY84-ARDUINO; SO14
U$1: QWIIC_5.5MM
U$2, U$20: QWIIC0
U$3, U$19: LED2
U$4: INT-()-04
U$5, U$14: SCL
U$6, U$12: SDA
U$7, U$22: 3.3V
U$8, U$13, U$16, U$17: GND
U$9: (ADR)
U$10: I_SUPER2_C-()-03
U$11, U$15: INT#-[_-04
U$18: SPARKX-MEDIUM
U$21: STAT1
U$23, U$24: BUTTON1
U$25: A00
U$26: A11
U$27: A22
U$28: A33

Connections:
3.3V: C2.1, INT0.2, J1.3, J2.2, J3.2, J7.2, JP3.2, R3.2, U4.1
ADR0: JP1.2, U4.3
ADR1: JP4.2, U4.2
ADR2: JP5.2, U4.12
ADR3: JP7.2, U4.11
GND: C2.2, D1.C, J1.4, J2.1, J3.1, J4.2, J7.6, JP1.1, JP4.1, JP5.1, JP7.1, U4.14
INT_R: INT0.1, R11.2
LED: J4.1, U4.6
MISO: J7.1, U4.8
unnamed: D1.A, R4.1
SCL: J1.1, J2.4, J3.4, J7.3, R2.1, U4.9
SCL_PU1: JP3.1, R2.2
SDA: J1.2, J2.3, J3.3, J7.4, R1.1, U4.7
SDA_PU1: JP3.3, R1.2
STAT: R4.2, U4.10
~INT: J5.1, R11.1, U4.13
~RST: J7.5, R3.1, U4.4

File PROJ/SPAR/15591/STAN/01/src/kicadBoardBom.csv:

"Id";"Designator";"Package";"Quantity";"Designation";"Supplier and ref";
1;"JP6,JP2,JP8,JP9";"MICRO-FIDUCIAL";4;"FIDUCIALUFIDUCIAL";;;
2;"U$10";"I_SUPER2_C-()-03";1;"";;;
3;"LOGO1";"OSHW-LOGO-MINI";1;"OSHW-LOGOMINI";;;
4;"U$25";"A00";1;"";;;
5;"U$17,U$8,U$13,U$16";"GND";4;"";;;
6;"U$26";"A11";1;"";;;
7;"U$24,U$23";"BUTTON1";2;"";;;
8;"JP5,JP4,JP1,JP7";"SMT-JUMPER_2_NO_SILK";4;"";;;
9;"JP3";"SMT-JUMPER_3_2-NC_TRACE_SILK";1;"";;;
10;"U$15,U$11";"INT#-[_-04";2;"";;;
11;"INT0";"SMT-JUMPER_2_NC_TRACE_SILK";1;"";;;
12;"U$20,U$2";"QWIIC0";2;"";;;
13;"U$9";"(ADR)";1;"";;;
14;"U$5,U$14";"SCL";2;"";;;
15;"U$6,U$12";"SDA";2;"";;;
16;"U$7,U$22";"3.3V";2;"";;;
17;"U$19,U$3";"LED2";2;"";;;
18;"U$4";"INT-()-04";1;"";;;
19;"J7";"2X3_TEST_POINTS";1;"ISP";;;
20;"U$18";"SPARKX-MEDIUM";1;"";;;
21;"U$27";"A22";1;"";;;
22;"U$28";"A33";1;"";;;
23;"D1";"LED-0603";1;"RED";;;
24;"U4";"SO14";1;"ATTINY84-ARDUINO";;;
25;"U$1";"QWIIC_5.5MM";1;"";;;
26;"FRAME1";"CREATIVE_COMMONS";1;"FRAME-LETTER";;;
27;"U$21";"STAT1";1;"";;;
28;"J5";"1X01_NO_SILK";1;"";;;
29;"R2,R1";"0603";2;"2.2k";;;
30;"C2";"0603";1;"0.1uF";;;
31;"R4";"0603";1;"1k";;;
32;"J4";"1X02_NO_SILK";1;"";;;
33;"R11,R3";"0603";2;"10k";;;
34;"J1";"1X04_NO_SILK";1;"";;;
35;"J3,J2";"JST04_1MM_RA";2;"";;;

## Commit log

2022-10-21 Created ADAF and SPAR projects.
2022-10-21 Copied board files.
2022-10-21 Added jsons.
2022-10-21 Images and readmes.
2022-10-22 Images added to readme, resolutions added.
2022-10-24 Csv and readme changes.
2022-10-24 Copied files over.
2022-10-24 Low numbers and iboms
2022-10-24 Moved kicad files.
2022-10-24 Moved some files to src/
2022-10-25 New kicad and resolutions.
2022-10-25 Rreadme update kicad pcb and schematics added.
2022-10-26 Parts from boms in.
2022-10-26 Added parts matching.
2022-10-26 Added semi functional table to tag display.
2022-10-26 Fixed up images?
2022-10-27 Added kicad schematics.
2022-10-28 Added roper OOMPinstances.
2022-10-28 Changed parts.
2022-10-28 OOMP parts list update.
2022-10-28 Changed default voltage on CAPC-0805-X-UF10
2022-10-28 Matched after some new VREG's
2022-10-28 Raw parts test.
2022-10-28 Fixed changing detailspartysRaws.
2022-10-28 Fixing up.
2022-10-28 Json's
2022-10-29 Readme's fixed up.
2022-10-30 Doing a bit.
2022-10-30 Full run fixup.
2022-10-30 Full update.
2022-11-01 Project run through.
2022-11-01 Matched some parts.
2022-11-01 Added projects.
2022-11-02 A couple of extras.
2022-11-03 A few new bits.
2022-11-03 Full parts oomp added.
2022-11-04 Changes.
2022-11-05 More board details.
2022-11-09 Bit of a rebase.
2022-11-10 Regenerated.
2022-11-10 Fixed duplicating parts lists.
2022-11-10 Quickly Adding Everything
2022-11-11 Fixed naming mistake.
2022-11-14 Project update.
2022-11-14 Readme fixup.
2022-11-15 Readme changes.
